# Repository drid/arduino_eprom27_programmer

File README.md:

# Programmer for EPROM 27 series (16-512) based on Arduino

Forked from https://github.com/walhi/arduino_eprom27_programmer

Compatible Chips List (not all chips are tested):

 * 27C16 (connects from 3 to 26 leg DIP28 socket)
 * 27C32 (connects from 3 to 26 leg DIP28 socket)
 * 27C64
 * 27C128
 * 27C256
 * 27C512

Before write, check programming voltage in datasheet

## Schematic

Based on the project: https://github.com/bouletmarc/BMBurner

PCB Built in KiCAD 7 using through hole components to preserve retro style

## Software

Software for PC written by Qt6.

Functions:

 * Read chip
 * Write chip
 * Verify and check for write (no bits to be set to 1)
 * Programming voltage control (for AVR in TQFP case)

## Changelog
### Rev 1.0
Migration of circuit from Eagle

### Rev 1.1
Add support for ID reading and EEPROM Erase

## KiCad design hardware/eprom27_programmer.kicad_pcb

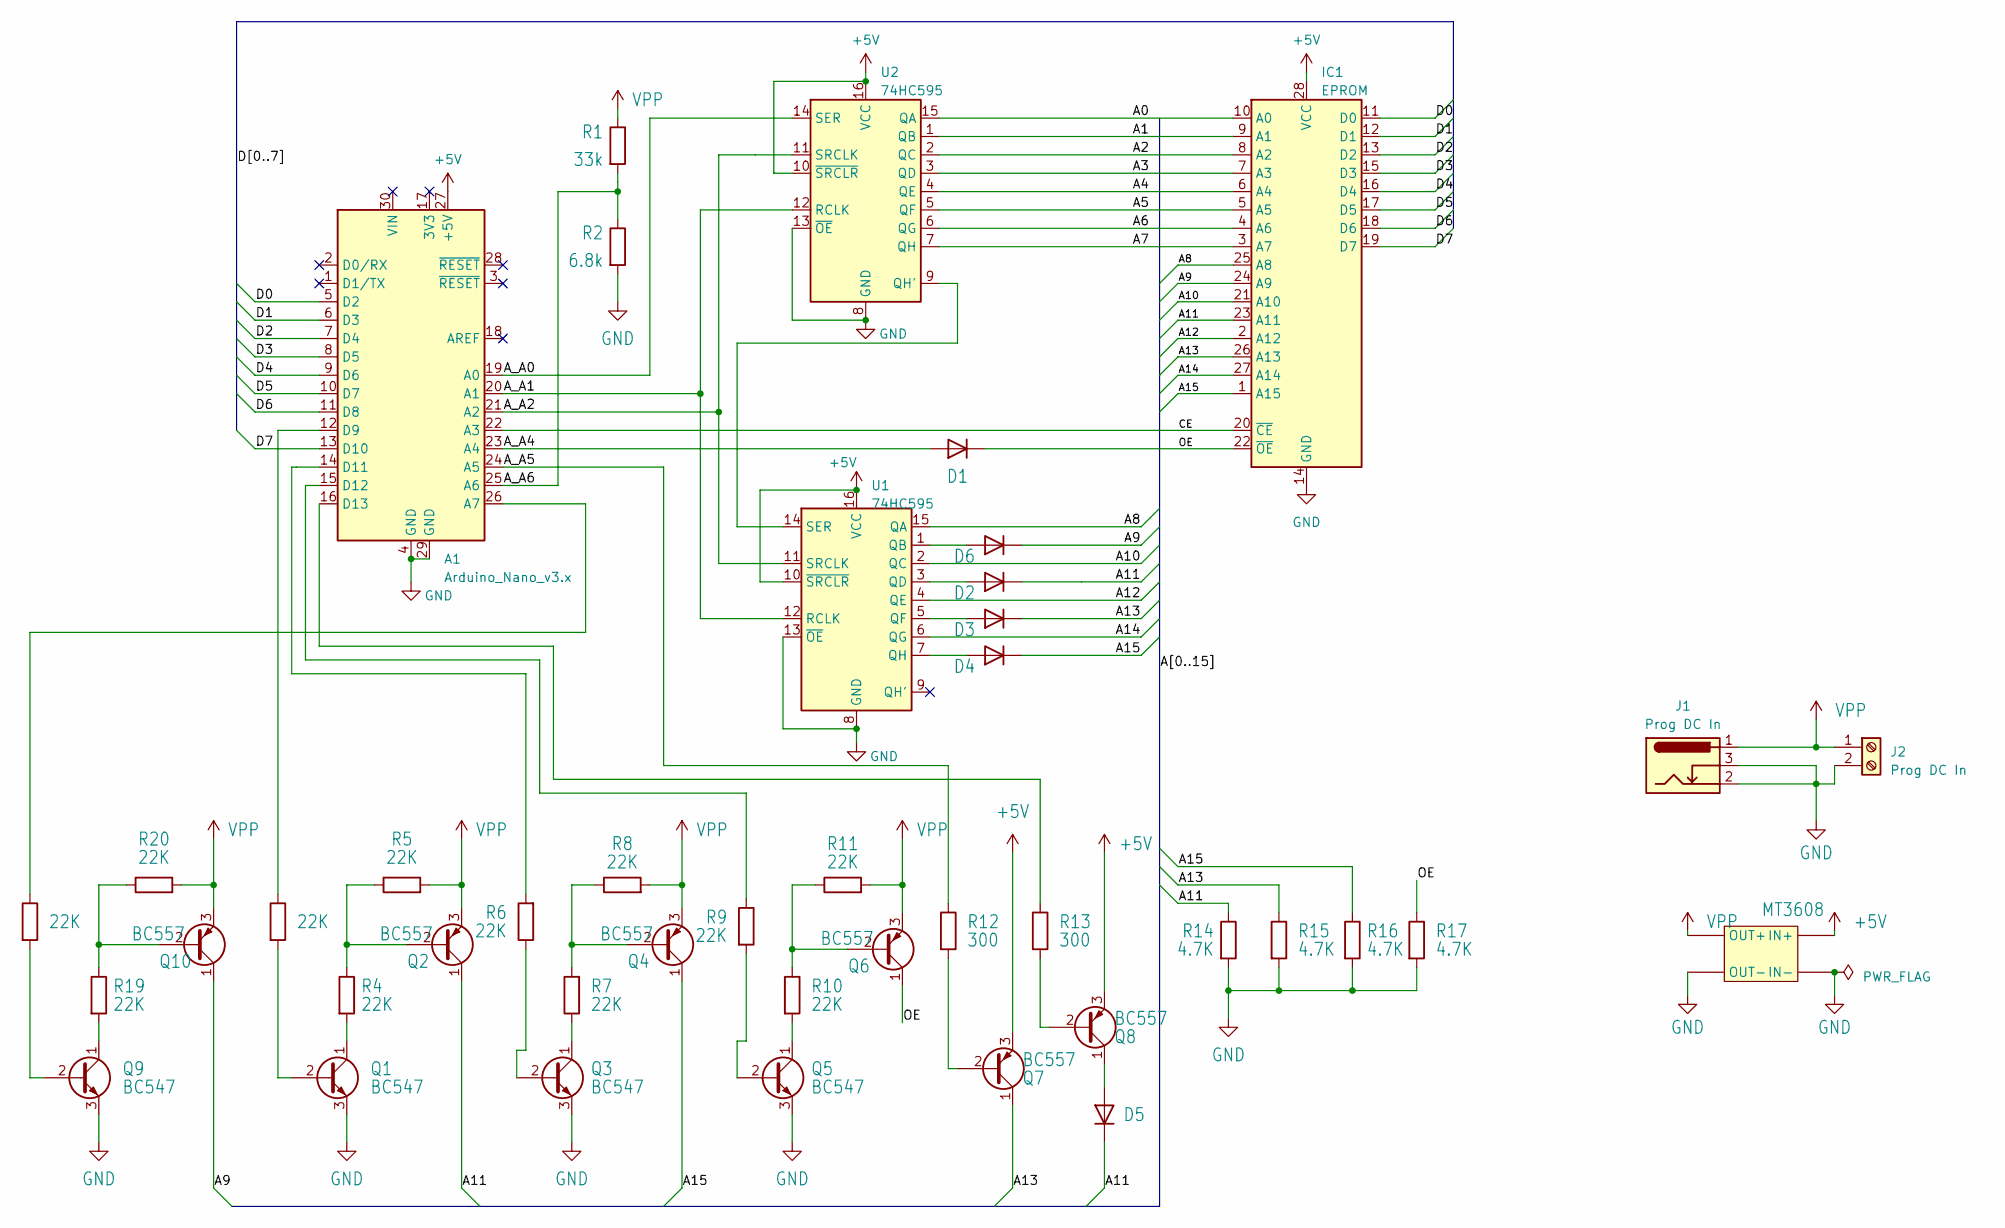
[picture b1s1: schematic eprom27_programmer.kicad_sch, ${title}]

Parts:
A1: Arduino_Nano_v3.x; Arduino_Nano
D1, D2, D3, D4, D5, D6: 1N4446; D_DO-35_SOD27_P7.62mm_Horizontal
IC1: EPROM; DIP_Socket-28_W11.9_W12.7_W15.24_W17.78_W18.5_3M_228-1277-0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
J1: Prog DC In; BarrelJack_Wuerth_6941xx301002
J2: Prog DC In; TerminalBlock_Phoenix_MKDS-1,5-2-5.08_1x02_P5.08mm_Horizont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
M1: MT3608; DC-DC-STEP-UP-MT3608
Q1, Q3, Q5, Q9: BC547; TO-92_Inline
Q2, Q4, Q6, Q7, Q8, Q10: BC557; TO-92_Inline
R1: 33k; R_Axial_DIN0207_L6.3mm_D2.5mm_P7.62mm_Horizontal
R2: 6.8k; R_Axial_DIN0207_L6.3mm_D2.5mm_P7.62mm_Horizontal
R3, R4, R5, R6, R7, R8, R9, R10, R11, R18, R19, R20: 22K; R_Axial_DIN0207_L6.3mm_D2.5mm_P7.62mm_Horizontal
R12, R13: 300; R_Axial_DIN0207_L6.3mm_D2.5mm_P7.62mm_Horizontal
R14, R15, R16, R17: 4.7K; R_Axial_DIN0207_L6.3mm_D2.5mm_P7.62mm_Horizontal
U1, U2: 74HC595; DIP-16_W7.62mm

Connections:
+5V: A1.27 (+5V), IC1.28 (VCC), M1.IN+, Q7.3 (E), Q8.3 (E), U1.10 (~SRCLR), U1.16 (VCC), U2.10 (~SRCLR), U2.16 (VCC)
/A0: IC1.10 (A0), U2.15 (QA)
/A1: IC1.9 (A1), U2.1 (QB)
/A2: IC1.8 (A2), U2.2 (QC)
/A3: IC1.7 (A3), U2.3 (QD)
/A4: IC1.6 (A4), U2.4 (QE)
/A5: IC1.5 (A5), U2.5 (QF)
/A6: IC1.4 (A6), U2.6 (QG)
/A7: IC1.3 (A7), U2.7 (QH)
/A8: IC1.25 (A8), U1.15 (QA)
/A9: D6.1 (K), IC1.24 (A9), Q10.1 (C)
/A10: IC1.21 (A10), U1.2 (QC)
/A11: D2.1 (K), D5.1 (K), IC1.23 (A11), Q2.1 (C), R14.1
/A12: IC1.2 (A12), U1.4 (QE)
/A13: D3.1 (K), IC1.26 (A13), Q7.1 (C), R15.1
/A14: IC1.27 (A14), U1.6 (QG)
/A15: D4.1 (K), IC1.1 (A15), Q4.1 (C), R16.1
/A_A0: A1.19 (A0), U2.14 (SER)
/A_A1: A1.20 (A1), U1.12 (RCLK), U2.12 (RCLK)
/A_A2: A1.21 (A2), U1.11 (SRCLK), U2.11 (SRCLK)
/A_A4: A1.23 (A4), D1.2 (A)
/A_A5: A1.24 (A5), R12.1
/A_A6: A1.25 (A6), R1.2, R2.1
/CE: A1.22 (A3), IC1.20 (~CE)
/D0: A1.5 (D2), IC1.11 (D0)
/D1: A1.6 (D3), IC1.12 (D1)
/D2: A1.7 (D4), IC1.13 (D2)
/D3: A1.8 (D5), IC1.15 (D3)
/D4: A1.9 (D6), IC1.16 (D4)
/D5: A1.10 (D7), IC1.17 (D5)
/D6: A1.11 (D8), IC1.18 (D6)
/D7: A1.13 (D10), IC1.19 (D7)
/OE: D1.1 (K), IC1.22 (~OE), Q6.1 (C), R17.1
GND: A1.4 (GND), A1.29 (GND), IC1.14 (GND), J1.2, J1.3, J2.2, M1.IN-, M1.OUT-, Q1.3 (E), Q3.3 (E), Q5.3 (E), Q9.3 (E), R2.2, R14.2, R15.2, R16.2, R17.2, U1.8 (GND), U1.13 (~OE), U2.8 (GND), U2.13 (~OE)
unnamed: A1.26 (A7), R18.1
unnamed: A1.12 (D9), R3.1
unnamed: A1.14 (D11), R6.2
unnamed: A1.15 (D12), R9.1
unnamed: A1.16 (D13), R13.1
unnamed: D2.2 (A), U1.3 (QD)
unnamed: D3.2 (A), U1.5 (QF)
unnamed: D4.2 (A), U1.7 (QH)
unnamed: D5.2 (A), Q8.1 (C)
unnamed: D6.2 (A), U1.1 (QB)
unnamed: Q1.2 (B), R3.2
unnamed: Q1.1 (C), R4.2
unnamed: Q2.2 (B), R4.1, R5.1
unnamed: Q3.2 (B), R6.1
unnamed: Q3.1 (C), R7.1
unnamed: Q4.2 (B), R7.2, R8.1
unnamed: Q5.2 (B), R9.2
unnamed: Q5.1 (C), R10.2
unnamed: Q6.2 (B), R10.1, R11.1
unnamed: Q7.2 (B), R12.2
unnamed: Q8.2 (B), R13.2
unnamed: Q9.2 (B), R18.2
unnamed: Q9.1 (C), R19.2
unnamed: Q10.2 (B), R19.1, R20.1
unnamed: U1.14 (SER), U2.9 (QH')
VPP: J1.1, J2.1, M1.OUT+, Q2.3 (E), Q4.3 (E), Q6.3 (E), Q10.3 (E), R1.1, R5.2, R8.2, R11.2, R20.2

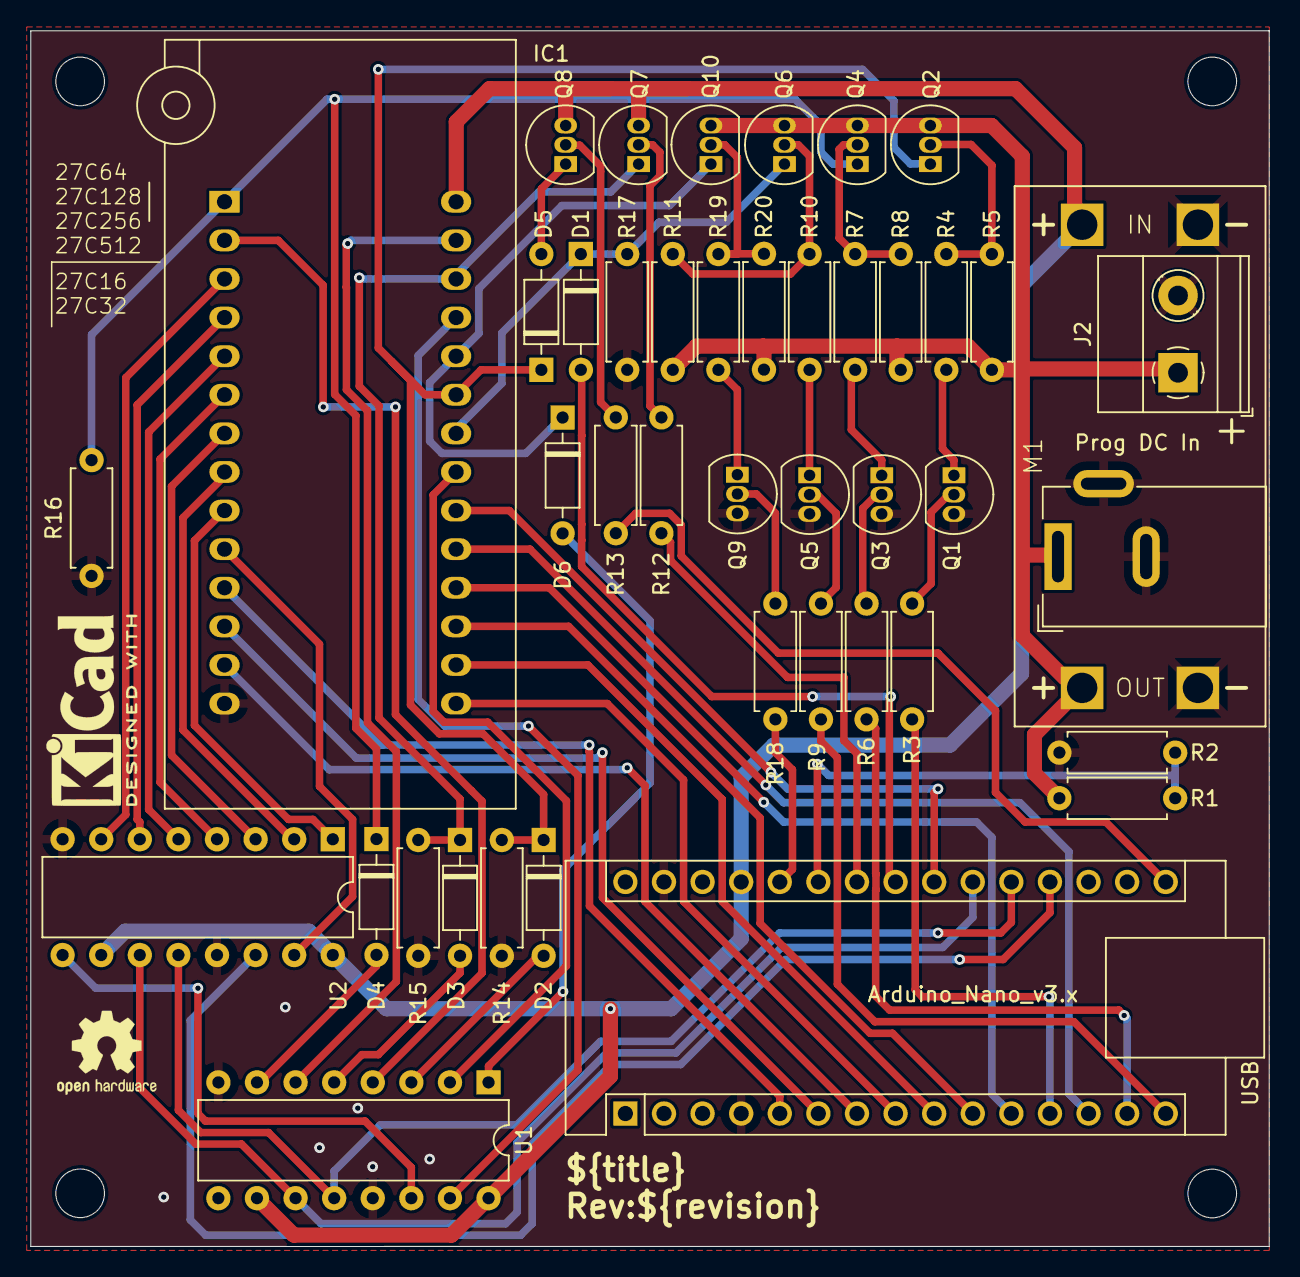
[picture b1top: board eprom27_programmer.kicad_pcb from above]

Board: 2 copper layers, 81.5 x 80.0 mm, 43 parts (0 on the bottom side), 60 nets.

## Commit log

2023-03-08 Eagle import
2023-03-08 Change symbols to KiCAD Symbols Change footrpints to KiCAD footprints Redesign as all through-hole components Update gitignore
2023-03-27 Fix write function Fix verify function Fix signals Fix table display
2023-03-27 Set ADC range to 30V
2023-03-28 Add hex dump function
2023-03-28 Add EPROM ID and EEPROM Erase connection
2024-01-08 Change voltage naming Update voltage divider Update README
